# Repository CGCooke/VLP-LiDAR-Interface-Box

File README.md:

# VLP-LiDAR-Interface-Box.
A replacement for the [VLP Interface box](https://velodynelidar.com/wp-content/uploads/2019/08/63-9259-REV-C-MANUALINTERFACE-BOXHDL-32EVLP-16VLP-32_Web-S.pdf).

Please see a [blog post on the project](https://cgcooke.github.io/posts/2023-01-12-Velodyne-Interface-Box.html) for more information.

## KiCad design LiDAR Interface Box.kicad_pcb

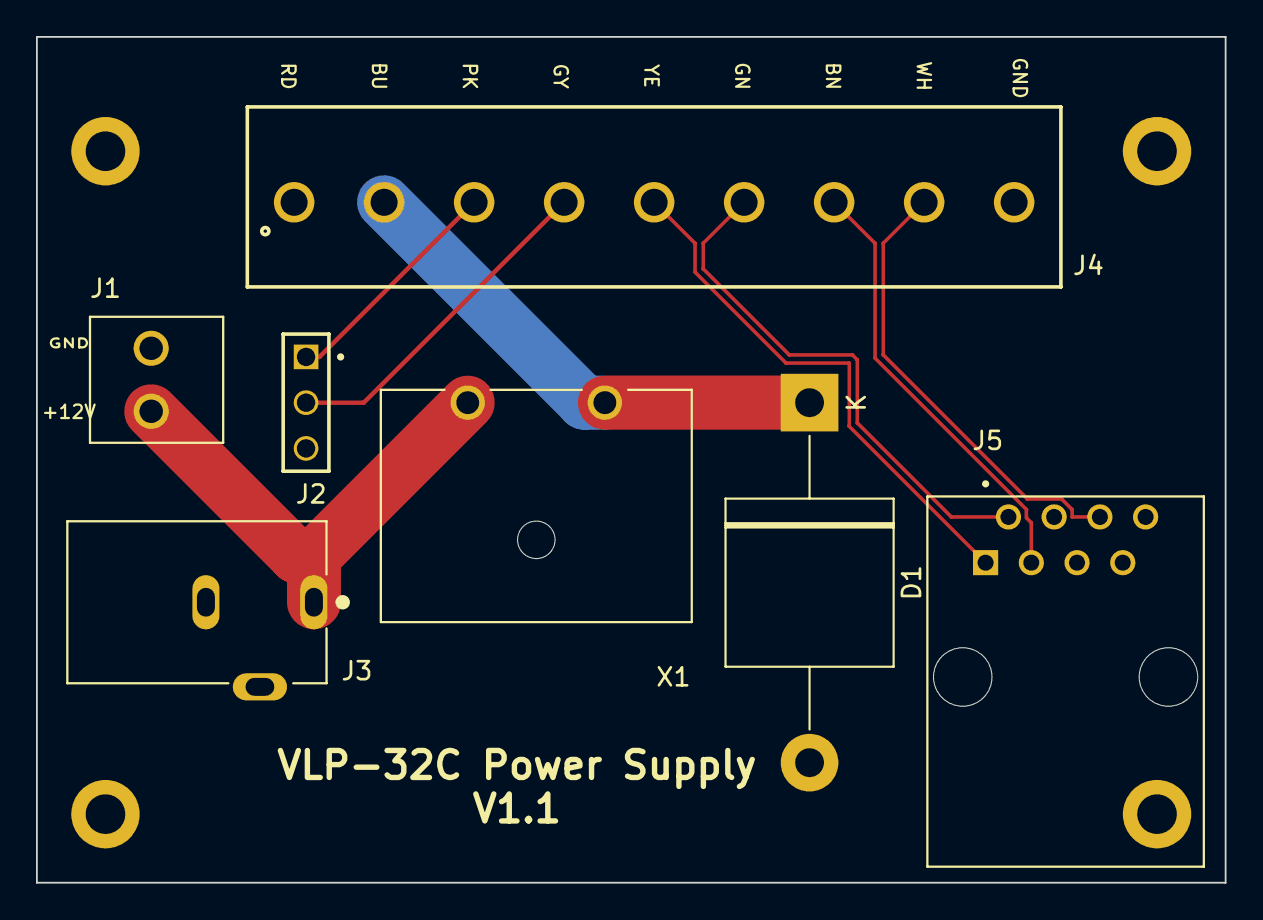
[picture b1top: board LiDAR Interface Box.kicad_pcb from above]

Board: 2 copper layers, 66.0 x 47.0 mm, 7 parts (0 on the bottom side), 9 nets.

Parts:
D1: 5KPxxA; D_P600_R-6_P20.00mm_Horizontal
J1: 691214110002
J2: TSW-101-26-L-T; SAMTEC_TSW-101-26-L-T
J3: PJ-102A; CUI_PJ-102A
J4: 691242710009
J5: SS-6488-NF; BEL_SS-6488-NF
X1: 01530007Z; FUSE_01530007Z

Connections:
+12V: D1.1 (A1), J4.2, X1.2
/12V_PRE_FUSE: J1.2, J3.1, X1.1
/ETHERNET_RX+: J4.7, J5.3
/ETHERNET_RX-: J4.8, J5.6
/ETHERNET_TX+: J4.5, J5.1
/ETHERNET_TX-: J4.6, J5.2
/GPS_PULSE_CNT: J2.01, J4.3
/GPS_RXD_CNT: J2.02, J4.4
GND: D1.2 (A2), J1.1, J2.03, J3.2, J4.1, J4.9

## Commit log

2023-01-11 Updated text size on PCB
2023-01-12 Updated Design.
2023-01-13 Updated the Readme.md
